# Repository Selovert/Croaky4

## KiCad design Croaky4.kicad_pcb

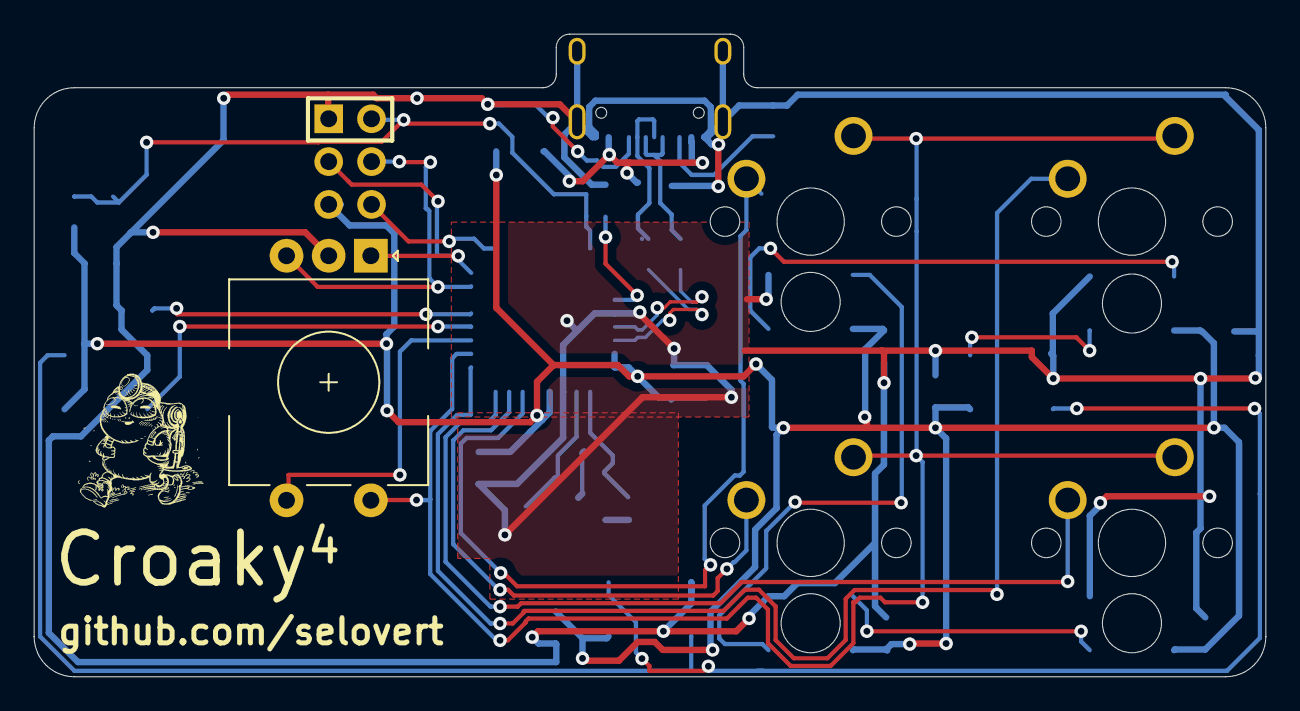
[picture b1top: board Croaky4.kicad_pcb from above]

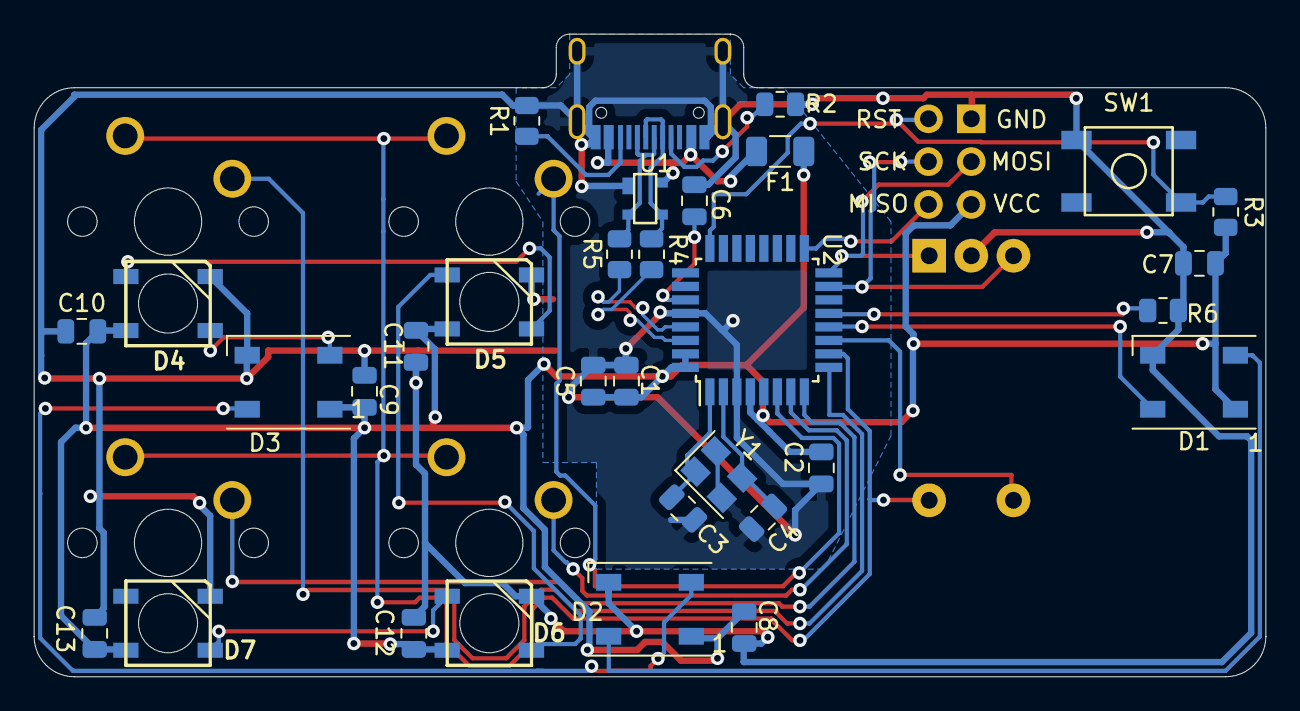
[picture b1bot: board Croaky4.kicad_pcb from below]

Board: 2 copper layers, 73.0 x 38.1 mm, 38 parts (32 on the bottom side), 30 nets.

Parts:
C1, C2: 0.1uF; C_0805_2012Metric
C3, C4: 22pF; C_0805_2012Metric
C5: 4.7uF; C_0805_2012Metric
C6: 1uF; C_0805_2012Metric
C7, C8, C9, C10, C11, C12, C13: .1uF; C_0805_2012Metric
D1, D2, D3: WS2812B; LED_WS2812B_PLCC4_5.0x5.0mm_P3.2mm
D4, D5, D6, D7: WS2812B; WS2812B_flipped
F1: 500mA; Fuse_1206_3216Metric
J1: AVR-ISP-6; Reset_Pretty-Mask
MX1, MX2, MX3, MX4: MX-LED; MXOnly-1U-NoLED
R1, R2: 5.1k; R_0805_2012Metric
R3, R6: 10k; R_0805_2012Metric
R4, R5: 22; R_0805_2012Metric
SW1: SW_Push; SKQG-1155865
SW2: Rotary_Encoder_Switch; RotaryEncoder_EC11
U1: PRTR5V0U2X; SOT143B
U2: ATmega32U2-AU; TQFP-32_7x7mm_P0.8mm
USB1: HRO-TYPE-C-31-M-12; HRO-TYPE-C-31-M-12-Assembly
Y1: 16MHz; Crystal_SMD_3225-4Pin_3.2x2.5mm

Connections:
+5V: C1.1, C2.1, C5.1, C7.2, C8.2, C9.2, C10.2, C11.2, C12.2, C13.2, D1.1, D2.1, D3.1, D4.1, D5.1, D6.1, D7.1, F1.1, J1.2, R3.2, U2.4, U2.31, U2.32
COL0: MX1.1, U2.6
COL1: MX2.1, U2.7
COL2: MX3.1, U2.9
COL3: MX4.1, U2.8
COL4: SW2.S1, U2.11
D+: R5.2, U2.29
D-: R4.1, U2.30
ENCA: J1.4, SW2.A, U2.16
ENCB: J1.3, SW2.B, U2.15
GND: C1.2, C2.2, C3.2, C4.2, C5.2, C6.2, C7.1, C8.1, C9.1, C10.1, C11.1, C12.1, C13.1, D1.3, D2.3, D3.3, D4.3, D5.3, D6.3, D7.3, J1.6, R1.2, R2.2, R6.1, SW1.1, SW2.C, U1.1, U2.3, U2.28, USB1.1, USB1.12, USB1.13, Y1.2, Y1.4
MISO: J1.1, U2.17
unnamed: C3.1, U2.1, Y1.1
unnamed: C4.1, U2.2, Y1.3
unnamed: C6.1, U2.27
unnamed: D1.2, D2.4
unnamed: D2.2, D3.4
unnamed: D3.2, D4.4
unnamed: D4.2, D5.4
unnamed: D5.2, D6.4
unnamed: D6.2, D7.4
unnamed: R1.1, USB1.10
unnamed: R2.1, USB1.4
unnamed: R4.2, U1.3, USB1.5, USB1.7
unnamed: R5.1, U1.2, USB1.6, USB1.8
unnamed: R6.2, U2.13
RESET: J1.5, R3.1, SW1.2, U2.24
RGBLED: D1.4, U2.12
ROW0: MX1.2, MX2.2, MX3.2, MX4.2, SW2.S2, U2.10
VCC: F1.2, U1.4, USB1.2, USB1.11

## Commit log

2021-03-06 initial project
2021-03-06 Add submodules
2021-03-07 added Keebio components
2021-03-07 added Keebio components for real
2021-03-07 renamed kicad proj and added switch footprints
2021-03-07 Schematic draft 1
2021-03-21 First prototype order
2021-04-04 Added R4 R5 labels
2021-04-15 DS_store to gitignore
2021-06-08 V1 hardware done
